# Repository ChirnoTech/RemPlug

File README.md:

RemPlug
==========
Esp8266 based Wi-fi smart plug

Specs:
- Input Voltage: 100-250V
- Current: 10A
- Wi-fi b/g/n
- MQTT, HTTP, etc controll

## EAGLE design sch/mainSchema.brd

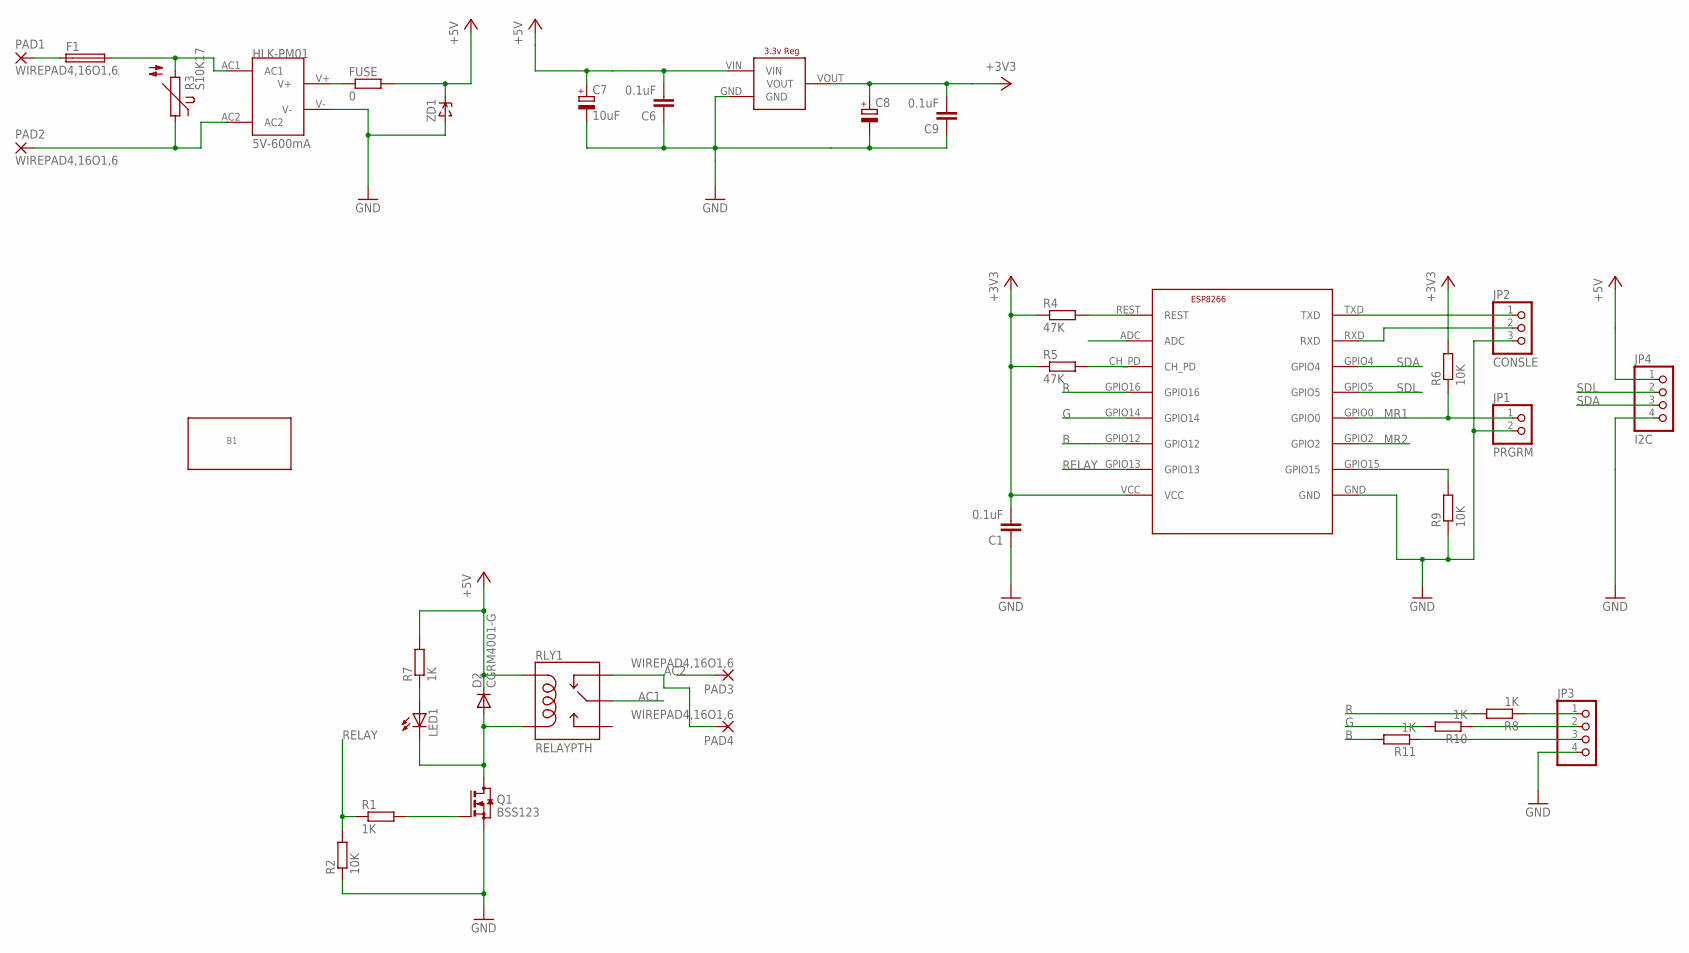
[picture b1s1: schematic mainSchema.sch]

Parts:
B1: VR1_POWER; VR1-POWER
C1, C6, C9: 0.1uF; C1206
C7: 10uF; PANASONIC_A
C8: CPOL-EUA; PANASONIC_A
D2: CGRM4001-G; SOD-123_MINI-SMA
ESP8266: ESP8266-07; ESP-07
F1: PICOFUSE
FUSE: 0; R1206
JP1: PRGRM; 1X02
JP2: CONSLE; 1X03
JP3: PINHD-1X4; 1X04
JP4: I2C; 1X04
LED1: LEDSMT1206; 1206
PAD1, PAD2, PAD3, PAD4: WIREPAD4,16O1,6; 4,16O1,6
Q1: BSS123; SOT23
R1, R7, R8, R10, R11: 1K; R0603
R2, R6, R9: 10K; R0603
R3: S10K17
R4, R5: 47K; R0603
RLY1: RELAYPTH; SRD-05VDC-SL-C
U$1: HILINK; HLK-PM01
U$5: LD1117; LD1117SOT-223
ZD1: ZENERSOD-123; SOD-123

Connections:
+3V3: C1.2, C8.+, C9.2, ESP8266.VCC, R4.1, R5.1, R6.2, U$5.VOUT
+5V: C6.2, C7.+, D2.C, FUSE.2, JP4.1, R7.2, RLY1.COIL1, U$5.VIN, ZD1.C
AC1: F1.2, R3.2, RLY1.SWCOMMON, U$1.AC1
AC2: PAD2.1, PAD3.1, R3.1, U$1.AC2
ADC: ESP8266.ADC
B: ESP8266.GPIO12, R11.2
G: ESP8266.GPIO14, R10.2
GND: C1.1, C6.1, C7.-, C8.-, C9.1, ESP8266.GND, JP1.2, JP2.3, JP3.4, JP4.4, Q1.2 (S), R2.1, R9.1, U$1.V-, U$5.GND, ZD1.A
MR1: ESP8266.GPIO0, JP1.1, R6.1
MR2: ESP8266.GPIO2
unnamed: PAD4.1, RLY1.SWCLOSED (SWCLOSE)
unnamed: F1.1, PAD1.1
unnamed: ESP8266.CH_PD, R5.2
unnamed: ESP8266.GPIO15, R9.2
unnamed: ESP8266.TXD, JP2.1
unnamed: ESP8266.RXD, JP2.2
unnamed: ESP8266.REST, R4.2
unnamed: FUSE.1, U$1.V+
unnamed: Q1.1 (G), R1.2
unnamed: D2.A, LED1.C, Q1.3 (D), RLY1.COIL0
unnamed: JP3.3, R11.1
unnamed: JP3.2, R10.1
unnamed: LED1.A, R7.1
unnamed: JP3.1, R8.1
R: ESP8266.GPIO16, R8.2
RELAY: ESP8266.GPIO13, R1.1, R2.2
SDA: ESP8266.GPIO4, JP4.3
SDL: ESP8266.GPIO5, JP4.2

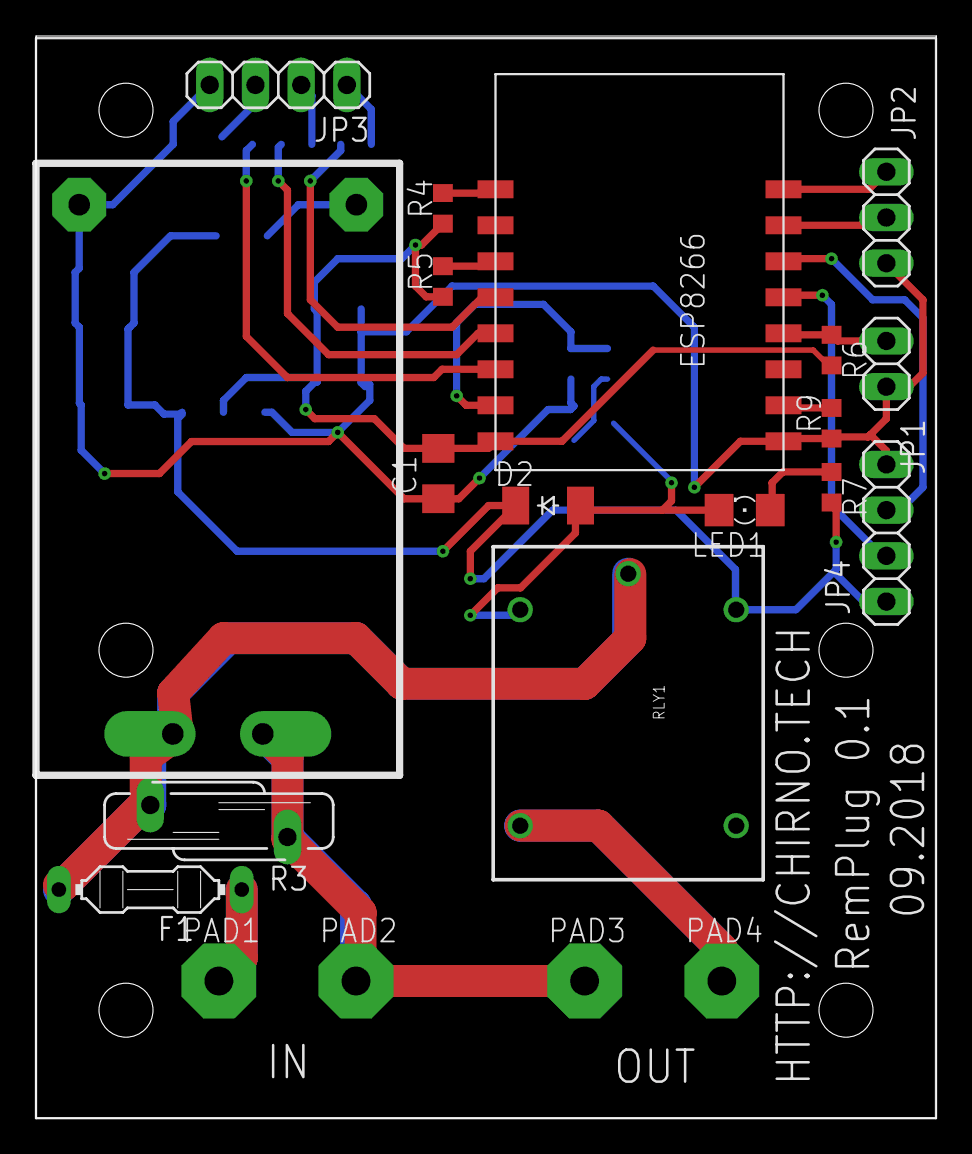
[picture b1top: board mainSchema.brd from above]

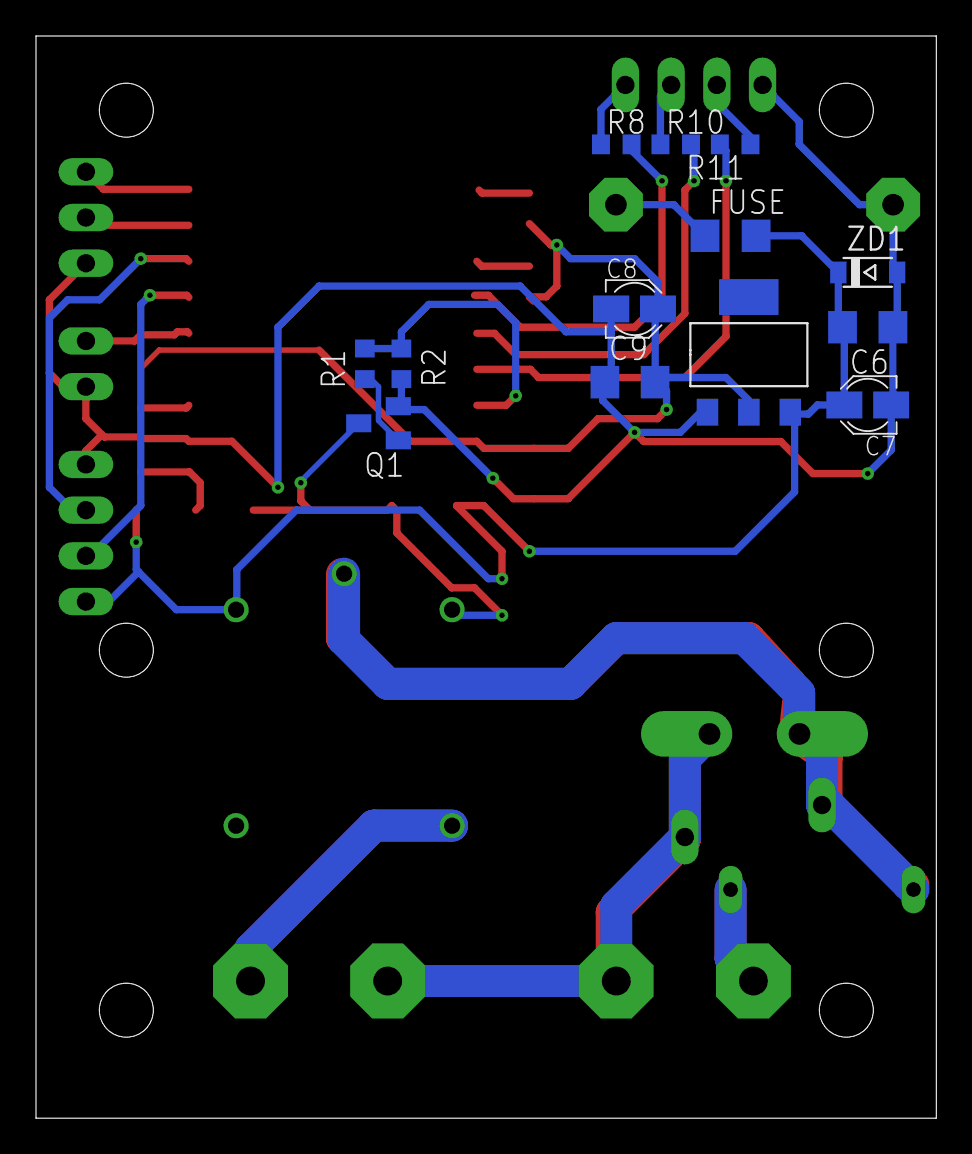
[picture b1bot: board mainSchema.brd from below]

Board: 2 copper layers, 50.0 x 60.1 mm, 35 parts (13 on the bottom side), 26 nets.

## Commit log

2018-10-20 First version
